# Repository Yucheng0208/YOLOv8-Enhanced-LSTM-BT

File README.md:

# YOLOv8 Pose and Object LSTM Bluetooth Combined

## Introduction
This project integrates **YOLOv8** for pose detection and object recognition, **LSTM (Long Short-Term Memory)** for sequential analysis, and **Bluetooth communication** for real-time interaction. It is designed to provide a robust solution for tracking and analyzing pose and object data in dynamic environments.

## Quick Start

This is my HackMD.io post about the [YOLOv8 Tutorial](https://hackmd.io/@Yucheng208/YOLOv8-Tutorial). It serves as a quick guide to help you get started efficiently. The content is written in Chinese and is user-friendly for Chinese-speaking readers. Feel free to refer to it for your learning needs!

---

## Features
- **Pose Detection**: Utilizing YOLOv8 for real-time pose estimation.
- **Object Recognition**: Detects objects in frames with high accuracy.
- **Sequential Analysis**: Implements LSTM to analyze pose and object sequences for pattern recognition.
- **Bluetooth Integration**: Enables wireless data transfer for real-time applications.
- **Customizable and Scalable**: Easily adaptable for different use cases, including sports analytics, robotics, and more.

---

## TODO List: Bluetooth Integration
This section outlines the tasks required to integrate Bluetooth communication into the project.

1. **Bluetooth Module Configuration**
   - [ ] Install and configure the Bluetooth module on your device (e.g., HC-05, HC-06, or similar).
   - [ ] Could you verify the module is discoverable and properly paired with your computer or target device?

2. **Connection Protocol**
   - [ ] Define the communication protocol for transferring pose and object data (e.g., JSON or CSV format).
   - [ ] Implement handshaking to ensure reliable data transfer between the device and the application.

3. **Bluetooth API**
   - [ ] Utilize `PyBluez` or an equivalent library for Python-based Bluetooth communication.
   - [ ] Implement basic Bluetooth functions:
     - [ ] Device scanning
     - [ ] Pairing and unpairing
     - [ ] Sending and receiving data

4. **Integration with YOLOv8 and LSTM**
   - [ ] Update the `main.py` script to send YOLOv8 and LSTM outputs to the paired Bluetooth device.
   - [ ] Design a feedback mechanism to receive acknowledgment or additional commands via Bluetooth.

5. **Testing and Debugging**
   - [ ] Test Bluetooth communication in a controlled environment with static and dynamic data.
   - [ ] Debug any latency or data loss issues during transfer.

6. **Documentation**
   - [ ] Document all configurations, including device names, UUIDs, and pairing codes.
   - [ ] Provide a user guide for setting up the Bluetooth environment.

---

## Installation
To set up the project, follow these steps:

1. Clone the repository:
   ```bash
   git clone https://github.com/Yucheng0208/YOLOv8_Pose_and_Object_LSTM_Bluetooth_Combined.git
   cd YOLOv8_Pose_and_Object_LSTM_Bluetooth_Combined
   ```

2. Create a Python virtual environment (optional but recommended):
   ```bash
   python -m venv venv
   source venv/bin/activate  # For Windows: venv\Scripts\activate
   ```

3. Install dependencies:
   ```bash
   pip install -r requirements.txt
   ```

4. Set up the environment:
   - Ensure that your device installs and configures the necessary Bluetooth modules.
   - Update the configuration file `config.yaml` with your device-specific parameters.

---

## Usage
1. Run the YOLOv8 pose and object detection module:
   ```bash
   python yolo_detection.py
   ```

2. Enable LSTM sequential analysis:
   ```bash
   python lstm_analysis.py
   ```

3. Start Bluetooth communication for data transfer:
   ```bash
   python bluetooth_transfer.py
   ```

4. Combine all modules:
   ```bash
   python main.py
   ```

---

## File Structure
```
YOLOv8-Enhanced-LSTM-BT/
│
├── data/                   # Sample datasets and testing data
├── models/                 # YOLOv8 and LSTM pre-trained models
├── scripts/                # Custom utility scripts
├── yolo_detection.py       # YOLOv8 pose and object detection
├── lstm_analysis.py        # LSTM sequential analysis
├── bluetooth_transfer.py   # Bluetooth communication script
├── main.py                 # Main program combining all modules
├── config.yaml             # Configuration file for parameters
└── requirements.txt        # Required Python libraries
```

## Citation
```
@inproceedings{tsai2024based,
  title={Using Real-Time Integrated Computer Vision and Deep Learning for Advanced Factory Safety},
  author={Tsai, Shang-Te and Chang, Yu-Cheng and Huang, Chao-Yi and Yang, Fang-Yuan and Chien, Wei and Wu, Zong-Rong},
  booktitle={2024 IEEE 4rd International Conference on Electronic Communications, Internet of Things and Big Data (ICEIB)},
  pages={647-649},
  year={2024},
  organization={IEEE},
  doi={10.1109/ICEIB61477.2024.10602722}
}}
```

---

## License
This project is licensed under the [MIT License](LICENSE).

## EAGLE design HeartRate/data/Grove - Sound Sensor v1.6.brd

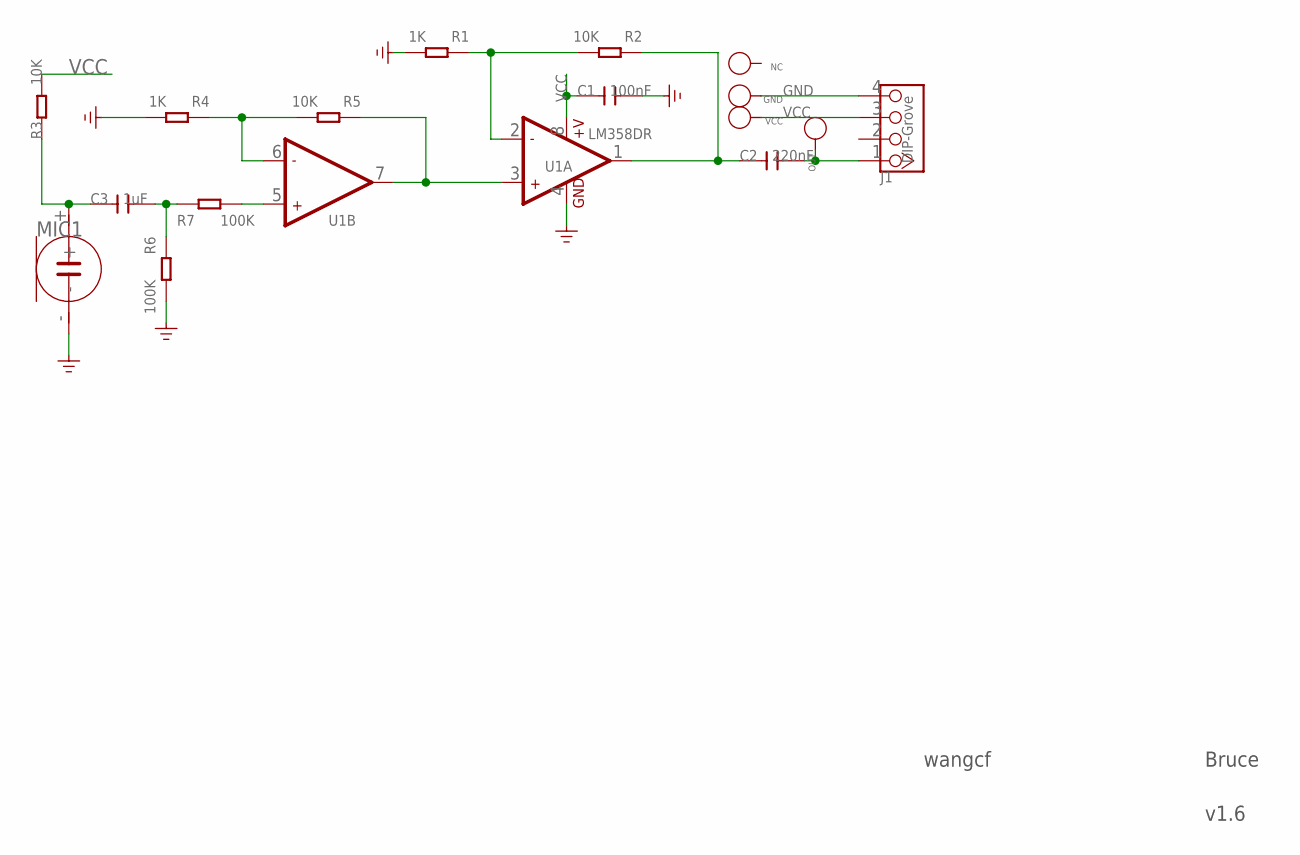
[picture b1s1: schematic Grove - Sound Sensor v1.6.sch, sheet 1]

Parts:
C1: 100nF; C0603
C2: 220nF; C0603
C3: 1uF; C0603
GND: PAD-TEST-POINT'4545'; TP_4545
J1: DIP-Grove; 4P-2.0
MIC1: MICROPHONE'KS-9745P,-56DB'; 2P-D9.7/4.5H
NC: PAD-TEST-POINT'4545'; TP_4545
OUT: PAD-TEST-POINT'4545'; TP_4545
R1, R4: 1K; R0603
R2, R3, R5: 10K; R0603
R6, R7: 100K; R0603
U1: LM358DR; SO08
VCC: PAD-TEST-POINT'4545'; TP_4545

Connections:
GND: C1.2, GND.T, J1.4, MIC1.-, R1.2, R4.2, R6.2, U1.4 (GND)
unnamed: R7.2, U1.5 (+IN2)
unnamed: R4.1, R5.2, U1.6 (-IN2)
unnamed: C3.2, R6.1, R7.1
unnamed: C3.1, MIC1.+, R3.1
unnamed: R5.1, U1.3 (+IN1), U1.7 (OUT2)
unnamed: R1.1, R2.2, U1.2 (-IN1)
OUT: C2.2, J1.1, OUT.T
OUT1: C2.1, R2.1, U1.1 (OUT1)
VCC: C1.1, J1.3, R3.2, U1.8 (+V), VCC.T

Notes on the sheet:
wangcf
Bruce
v1.6

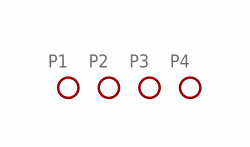
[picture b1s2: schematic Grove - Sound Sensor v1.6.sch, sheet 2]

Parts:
P1, P2, P3, P4: PAD-MARK; ROUND-MARK-1.0

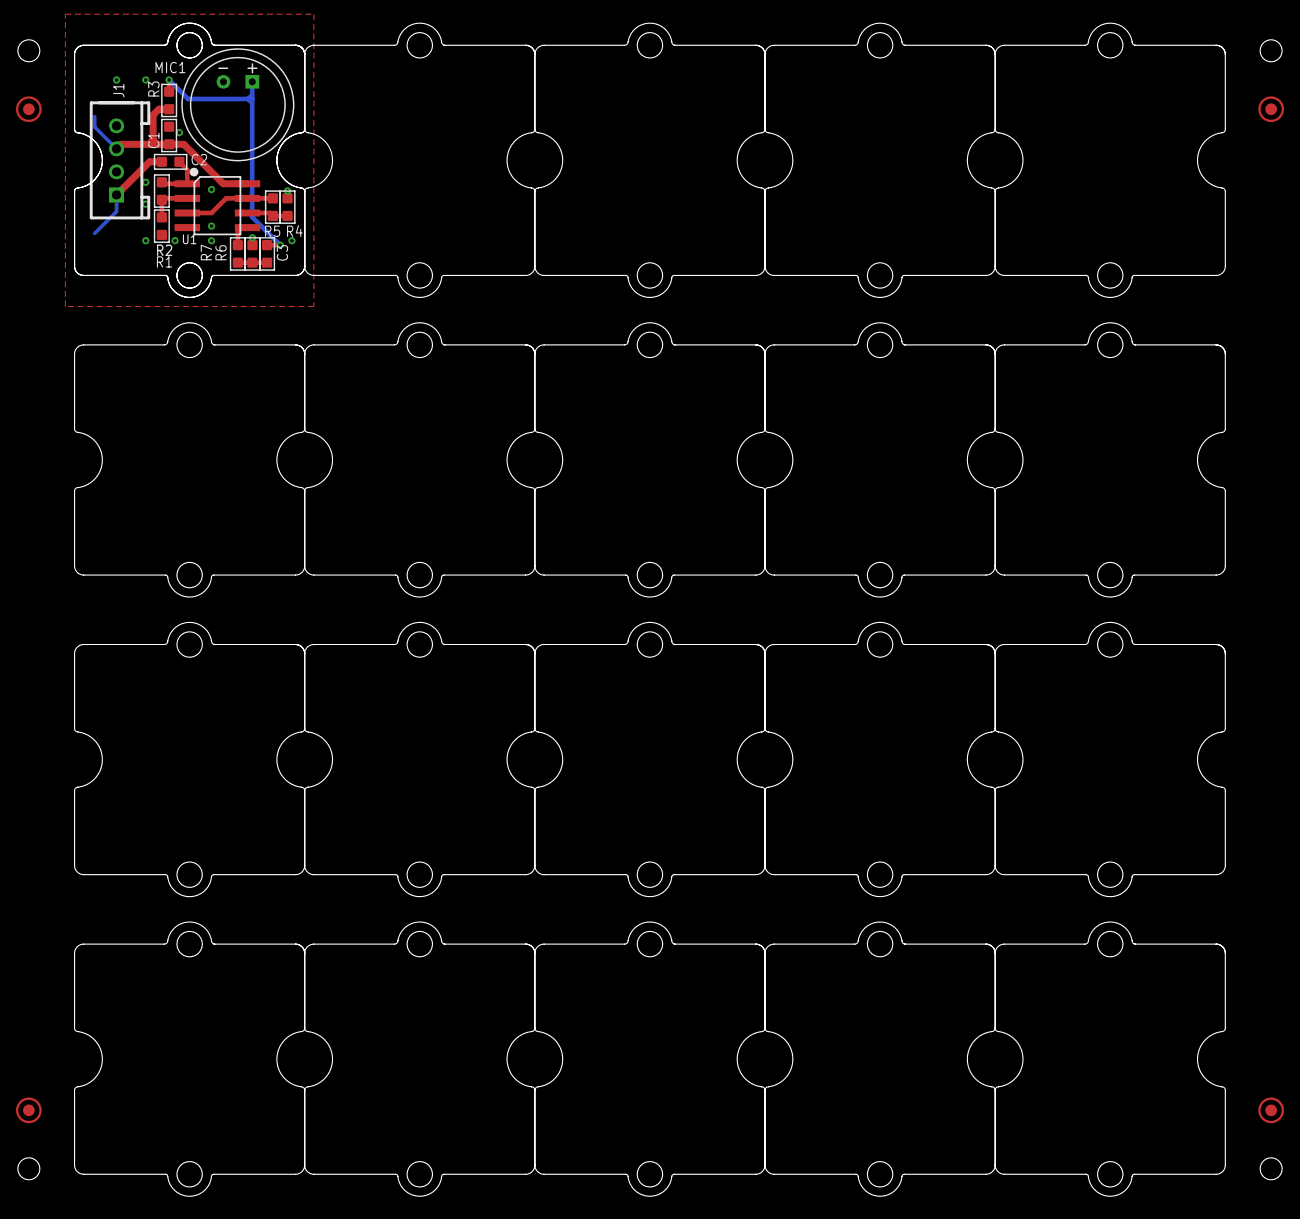
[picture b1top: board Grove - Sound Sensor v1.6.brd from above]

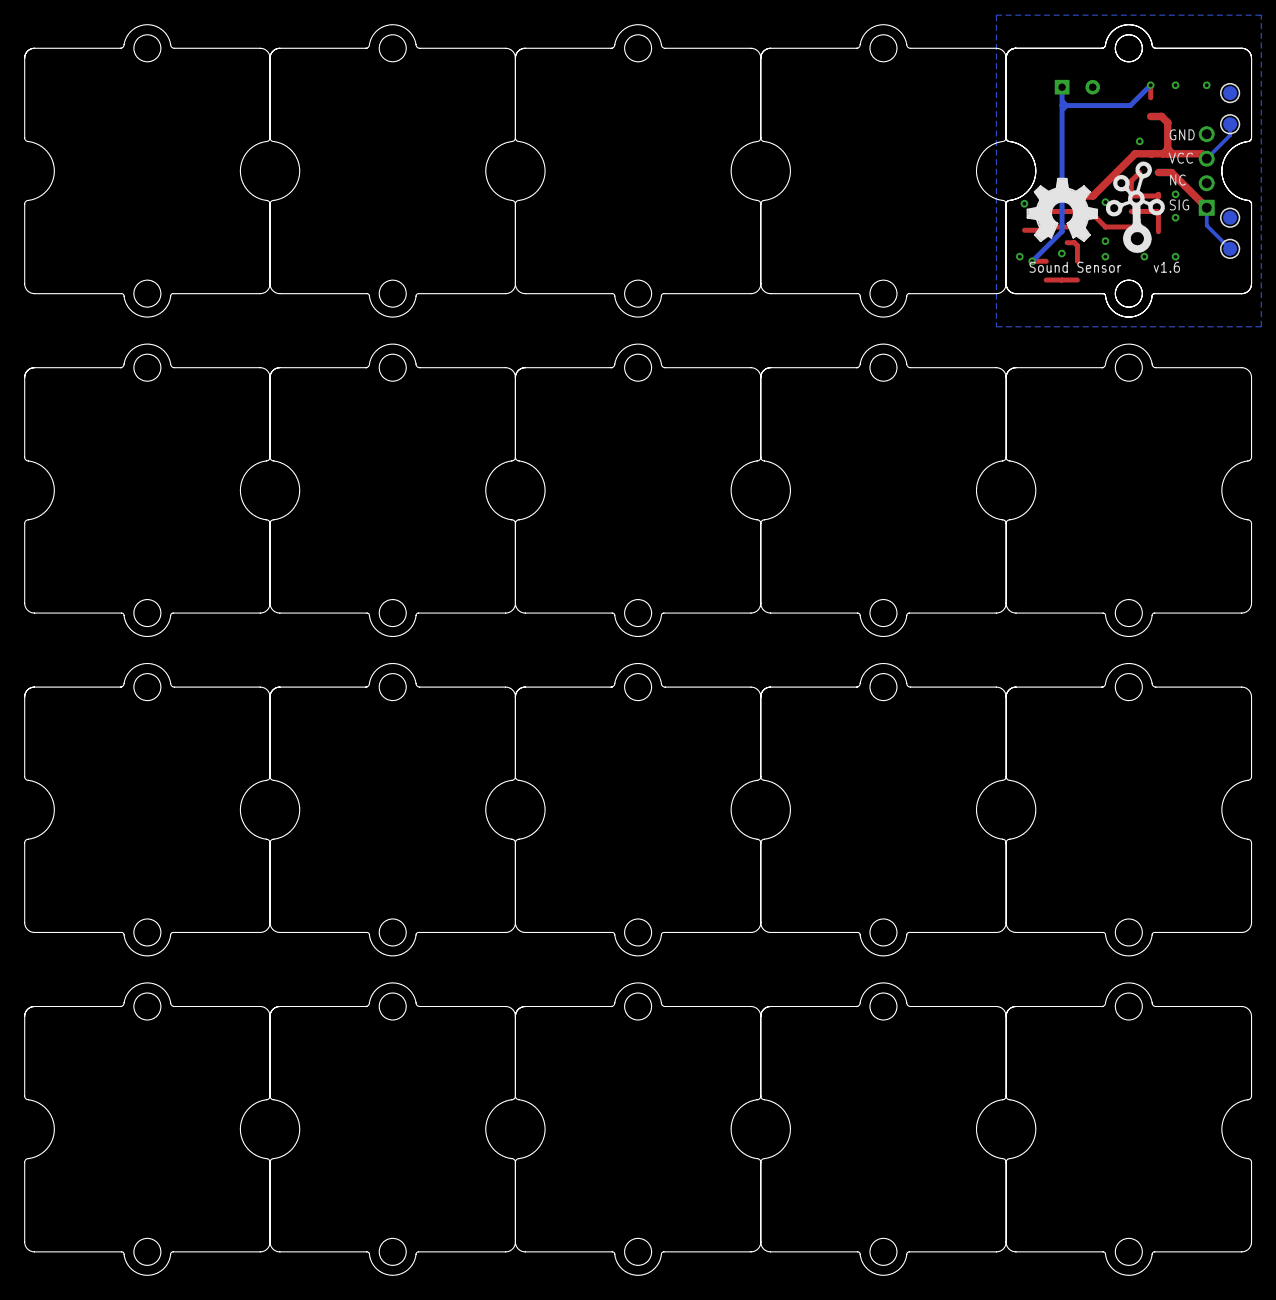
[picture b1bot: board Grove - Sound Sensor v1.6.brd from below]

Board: 2 copper layers, 100.0 x 101.9 mm, 44 parts (6 on the bottom side), 10 nets.

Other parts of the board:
U$1: OSHW_FILLX200_NOTEXT
U$4, U$12, U$13, U$14, U$15, U$16, U$17, U$18, U$19, U$20, U$21, U$22, U$23, U$24, U$25, U$26, U$27, U$28, U$29, U$30, U$31: 1U-DIM-W/-DRILL
U$7: TWIGLOGO

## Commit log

2024-11-22 Split tensor_data.npy
2024-11-22 add lstm program files
2024-11-22 add video
2024-11-22 add helmet detection code
2024-11-22 add Heart Rate files
2024-11-22 add bluetooth sample code
